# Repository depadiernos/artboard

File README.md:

# Artboard

A small keyboard design for those who cannot or prefer not use 'traditional' keyboard designs. This keyboard is inspired by [The Paintbrush](https://github.com/artseyio/thepaintbrush)

*This project aims to create a small keyboard design that is adaptable and flexible. Especially for those with disabilities, those who cannot type on traditional keyboads and those that prefer not use traditional keyboards.*

## What

A small keyboard hardware design that can be built free of charge for non-commercial use. The design is meant to be used with systems like [ARTSEY.IO](https://www.artsey.io/).

We also work to have our hardware supported by well known open source keyboard firmware projects to make them easier to setup and use.

## Who

I'm a software engineer by trade. I hurt my right elbow (tennis elbow) and have been looking for a one-handed keyboard so I can rest my right arm so it can hopefully heal faster.

## Licensing

Unless otherwise stated all source code is licensed under the [Apache 2 License](LICENSE-APACHE-2.0.txt).

Unless otherwise state all hardware designs are licensed under the [CERN Open Hardware Licence Version 2 - Weakly Reciprocal License](LICENSE-cern_ohl_w_v2.txt).

Unless otherwise stated the non source code and non hardware design contents of this repository are licensed under a [Creative Commons Attribution-NonCommercial-ShareAlike 4.0 International License](LICENSE-CC-Attribution-NonCommercial-ShareAlike-4.0-International.txt)

## Commercial Licencing

If you're interested in commercial licencing of our designs, please contact depadiernos for details. Their e-mail can be found in the git log. When contacting depadiernos please include (at a minimum) your name, your company/store's website, how you plan to sell the designs and why you'd like to sell the designs.

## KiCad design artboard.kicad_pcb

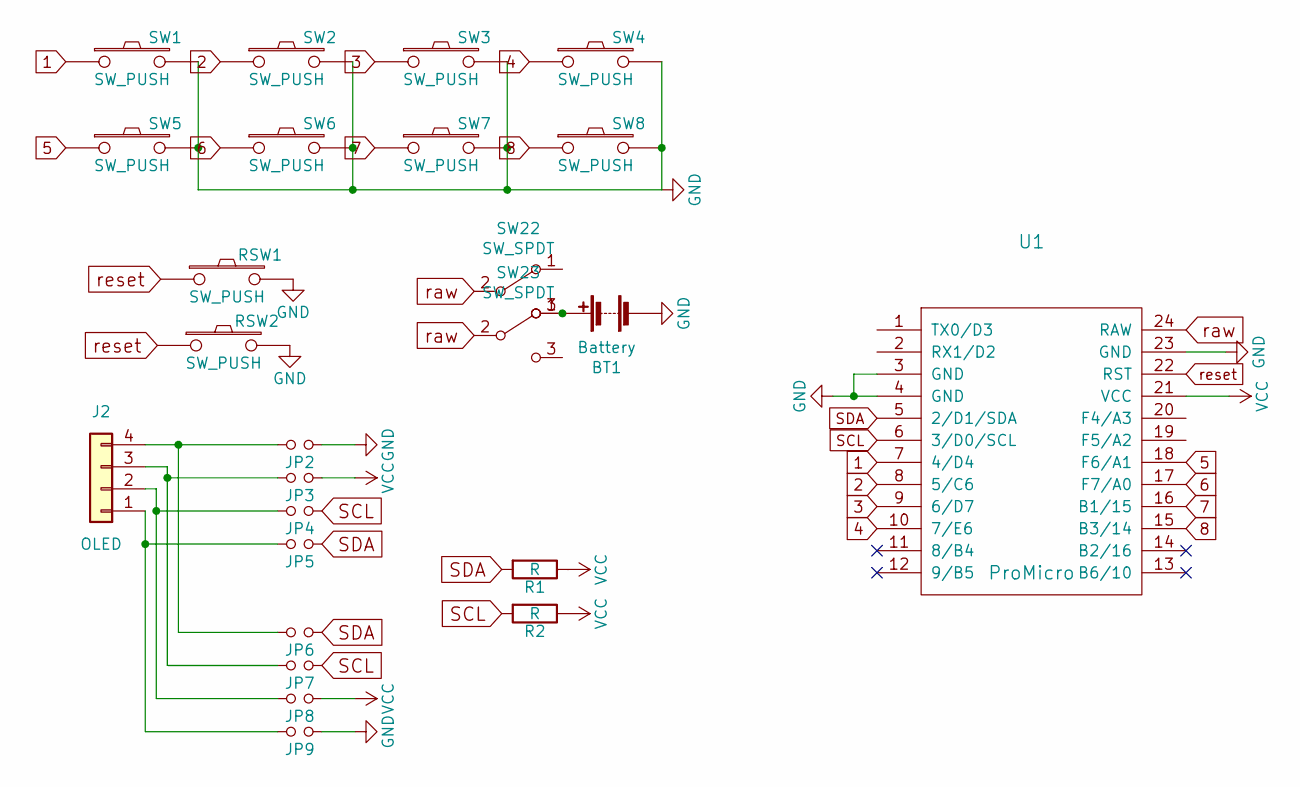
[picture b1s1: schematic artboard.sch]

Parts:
BT1: Battery; PinHeader_1x02_P2.00mm_Vertical
J2: OLED
JP2, JP3, JP4, JP5, JP6, JP7, JP8, JP9: Jumper
R1, R2: R; R_0603_1608Metric_Pad0.98x0.95mm_HandSolder
RSW1, RSW2: SW_PUSH; SW_SPST_B3U-3000P
SW1, SW2, SW3, SW4, SW5, SW6, SW7, SW8: SW_PUSH; ChocV1_V2_Hotswap
SW22, SW23: SW_SPDT; SW_SPDT_PCM12
U1: ProMicro; ProMicro_Jumper

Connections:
1: SW1.1, U1.7 (4/D4)
2: SW2.1, U1.8 (5/C6)
3: SW3.1, U1.9 (6/D7)
4: SW4.1, U1.10 (7/E6)
5: SW5.1, U1.18 (F6/A1)
6: SW6.1, U1.17 (F7/A0)
7: SW7.1, U1.16 (B1/15)
8: SW8.1, U1.15 (B3/14)
GND: BT1.2 (-), JP2.1, JP9.1, RSW1.2, RSW2.2, SW1.2, SW2.2, SW3.2, SW4.2, SW5.2, SW6.2, SW7.2, SW8.2, U1.3 (GND), U1.4 (GND), U1.23 (GND)
unnamed: BT1.1 (+), SW22.3 (C), SW23.1 (A)
unnamed: J2.1, JP5.2, JP9.2
unnamed: J2.2, JP4.2, JP8.2
unnamed: J2.3, JP3.2, JP7.2
unnamed: J2.4, JP2.2, JP6.2
SCL: JP4.1, JP7.1, R2.2, U1.6 (3/D0/SCL)
SDA: JP5.1, JP6.1, R1.2, U1.5 (2/D1/SDA)
VCC: JP3.1, JP8.1, R1.1, R2.1, U1.21 (VCC)
raw: SW22.2 (B), SW23.2 (B), U1.24 (RAW)
reset: RSW1.1, RSW2.1, U1.22 (RST)

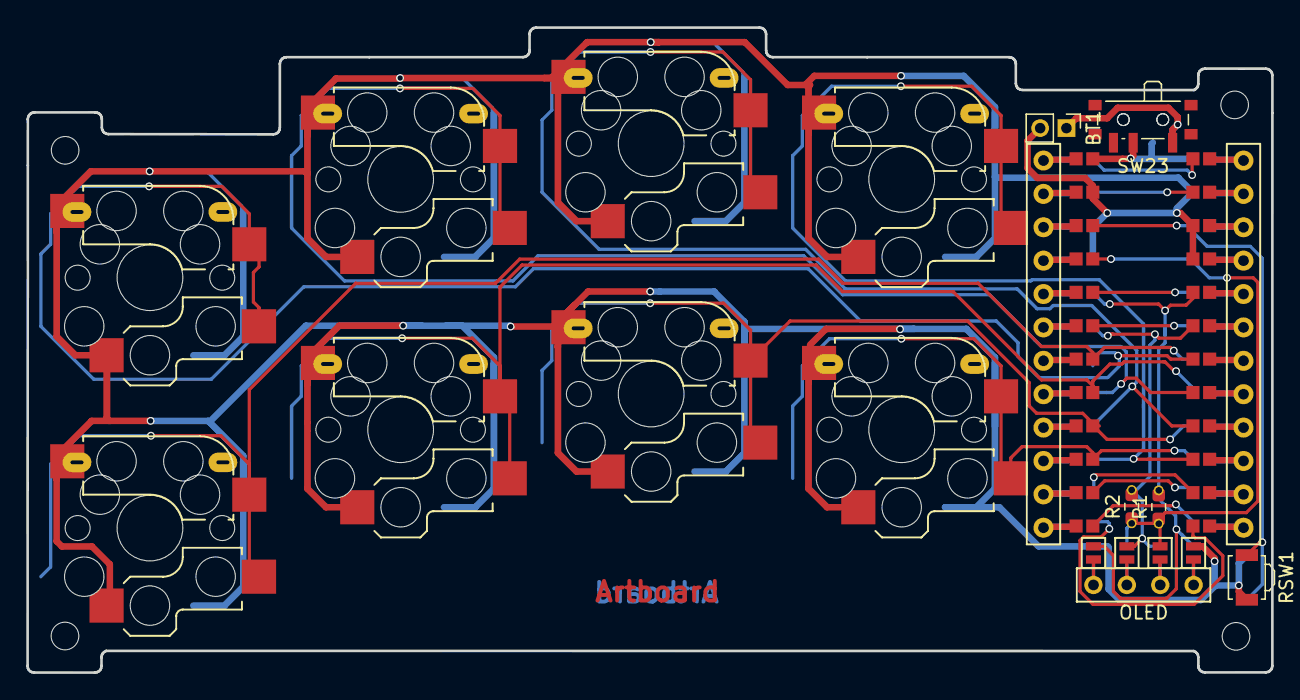
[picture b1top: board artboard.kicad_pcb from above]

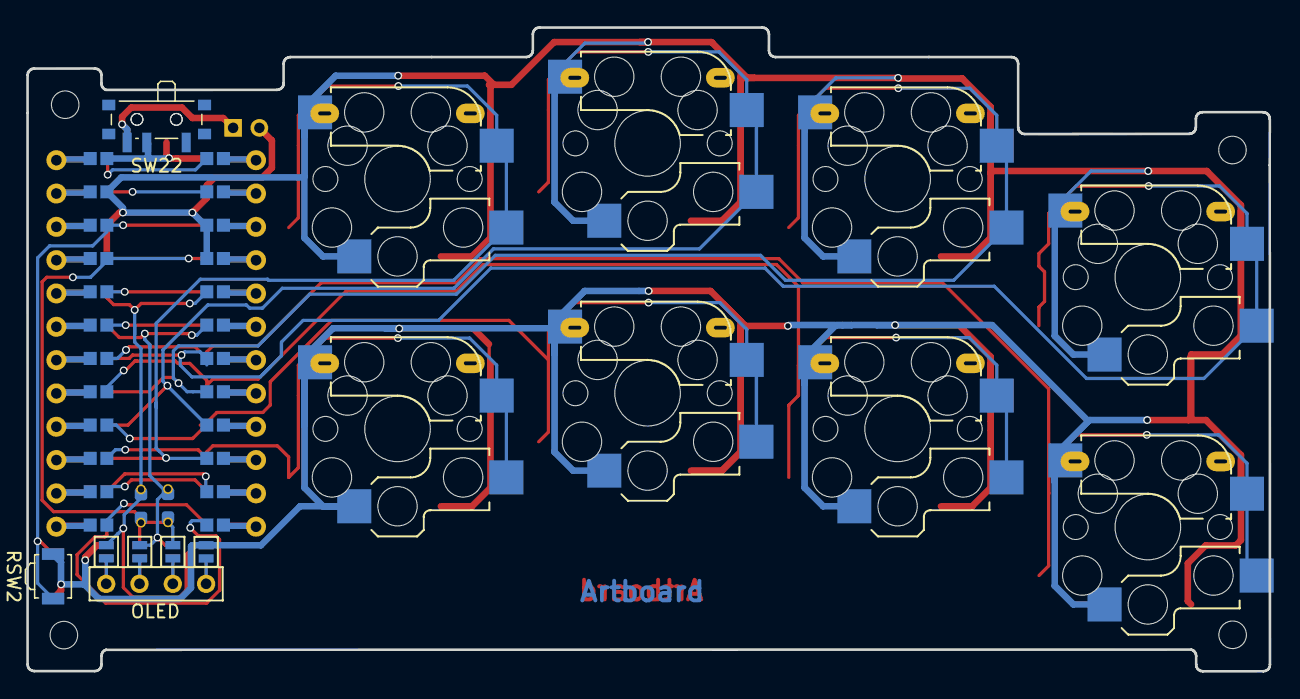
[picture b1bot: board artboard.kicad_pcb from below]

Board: 2 copper layers, 94.7 x 49.1 mm, 29 parts (6 on the bottom side), 19 nets.

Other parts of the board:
Ref**: Val**; MountingHole_2.1mm
Ref**#2, Ref**#3, Ref**#4: Val**; MountingHole_2.1mm

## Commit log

2021-04-19 fix symbol library
2021-04-20 add license and gitignore. remove bak files
2021-04-20 fix some rescued symbols
2021-04-20 Add repo README.md
2021-04-20 fix a link in README.md
2021-04-20 un-nest pcb folder
2021-04-22 generate gerber files
2021-04-24 add mounting holes
2021-04-24 route last dangling pads
